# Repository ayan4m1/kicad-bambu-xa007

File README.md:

# Open Source Power Switch Module

This is intended to serve as an OSHW version of Bambu Labs' XA007 Power Switch Module.

# Schematic

# PCB

# BOM

| SKU          | Description      | Qty | Buy                                                             |
|--------------|------------------|-----|-----------------------------------------------------------------|
| S2B-XH-ALFSN | Power connectors | 2   | [Mouser](https://www.mouser.com/ProductDetail/306-S2B-XH-ALFSN) |
| X3P2D        | Toggle switch    | 1   | [Amazon](https://www.amazon.com/dp/B075RDYMQQ)                  |

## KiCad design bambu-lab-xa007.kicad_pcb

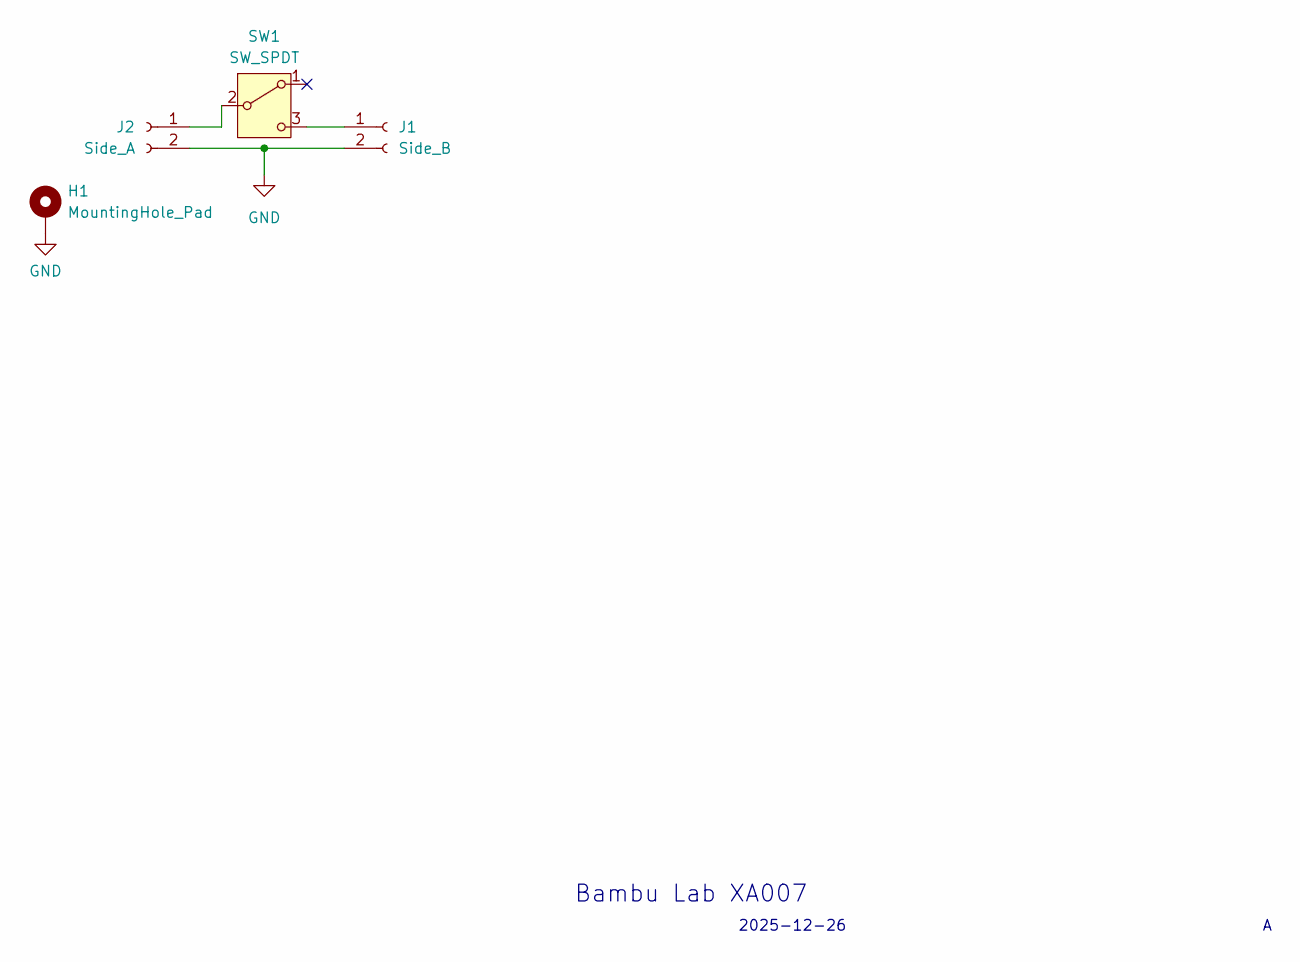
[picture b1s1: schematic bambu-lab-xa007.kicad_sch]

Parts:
H1: MountingHole_Pad; MountingHole_2.7mm_M2.5_Pad_TopBottom
J1: Side_B; JST_XH_S2B-XH-A_1x02_P2.50mm_Horizontal
J2: Side_A; JST_XH_S2B-XH-A_1x02_P2.50mm_Horizontal
SW1: SW_SPDT; MICRO-SWITCH

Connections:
GND: H1.1, J1.2, J2.2
unnamed: J1.1, SW1.3 (C)
unnamed: J2.1, SW1.2 (B)

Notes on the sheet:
2025-12-26
Bambu Lab XA007

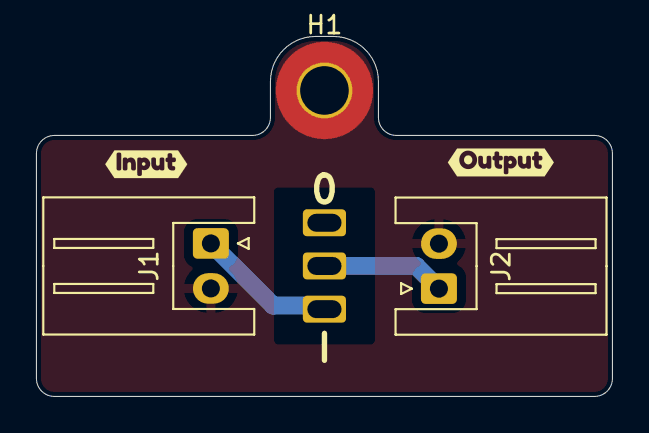
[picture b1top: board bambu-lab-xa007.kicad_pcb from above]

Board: 2 copper layers, 32.0 x 20.0 mm, 6 parts (0 on the bottom side), 3 nets.

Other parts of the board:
kibuzzard-6990D6AA: G***; kibuzzard-6990D6AA
kibuzzard-6990D6B8: G***; kibuzzard-6990D6B8

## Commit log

2026-02-15 feat: initial import
2026-02-15 docs: add README.md and screenshots
2026-02-15 docs: add LICENSE
2026-02-15 docs: add BOM to README.md
2026-02-15 fix: correct 1 and 0 text under switch
2026-02-15 docs: update pcb screenshot with new text positions
2026-02-27 fix: modify footprint for mounting hole to be M2.5
2026-03-23 fix footprint for SPDT switch
2026-03-23 update pcb screenshot
